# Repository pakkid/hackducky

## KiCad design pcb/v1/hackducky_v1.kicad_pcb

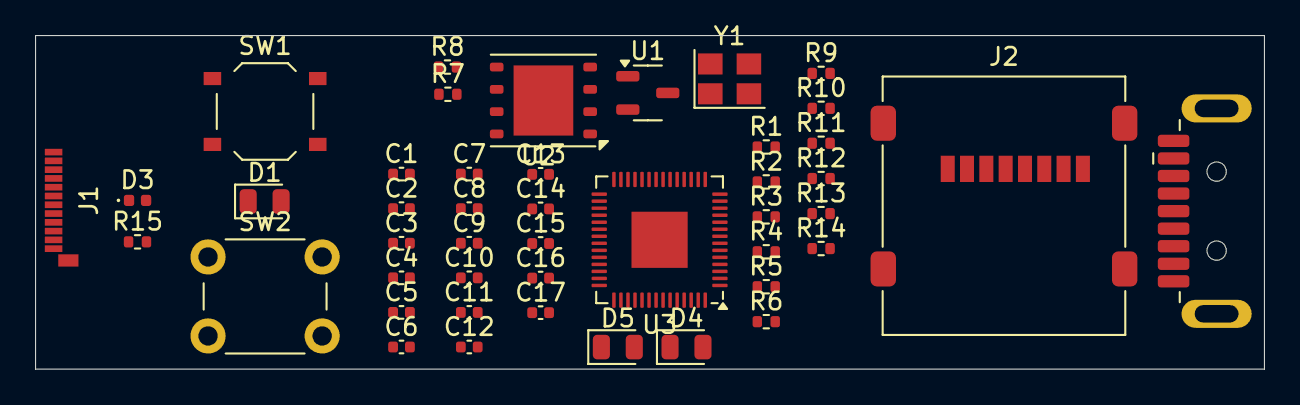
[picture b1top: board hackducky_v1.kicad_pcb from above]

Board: 2 copper layers, 70.0 x 19.0 mm, 45 parts (0 on the bottom side), 32 nets, no tracks yet.

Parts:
C1, C2: 15p; C_0402_1005Metric
C3, C4, C9, C10: 1u; C_0402_1005Metric
C5: 10u; C_0402_1005Metric
C6, C7, C8, C11, C12, C13, C14, C15, C16, C17: 100n; C_0402_1005Metric
D1: LED; LED_0805_2012Metric
D3: LED; LED_0402_1005Metric
D4, D5: S-LMBR340FT1G; D_0805_2012Metric
J1: USB_C_Receptacle_USB2.0_16P; USB_C_Plug_Molex_105444
J2: Micro_SD_Card; microSD_HC_Molex_47219-2001
J3: USB_A; USB3_A_Plug_Wuerth_692112030100_Horizontal
R1, R2: 5.1k; R_0402_1005Metric
R3, R5: 1k; R_0402_1005Metric
R4: 330; R_0402_1005Metric
R6: DNF; R_0402_1005Metric
R7, R8: 27.4; R_0402_1005Metric
R9, R10, R11, R12, R13, R14: 10k; R_0402_1005Metric
R15: 330?; R_0402_1005Metric
SW1: SW_Push; SW_Push_1P1T_XKB_TS-1187A
SW2: SW_Push; SW_PUSH_6mm
U1: XC6206PxxxMR; SOT-23-3
U2: W25Q64JVZPIQ; WSON-8-1EP_6x5mm_P1.27mm_EP3.4x4mm
U3: RP2040; QFN-56-1EP_7x7mm_P0.4mm_EP3.2x3.2mm
Y1: Crystal_GND23; Crystal_SMD_Abracon_ABM8G-4Pin_3.2x2.5mm

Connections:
+1V1: C7.1, C8.1, C9.1, U3.23 (DVDD), U3.45 (VREG_VOUT), U3.50 (DVDD)
+3V3: C4.1, C5.1, C6.1, C10.1, C11.1, C12.1, C13.1, C14.1, C15.1, C16.1, C17.1, J2.4 (VDD), R6.1, R9.1, R10.1, R11.1, R12.1, R13.1, R14.1, U1.2 (VO), U2.8 (VCC), U3.1 (IOVDD), U3.10 (IOVDD), U3.22 (IOVDD), U3.33 (IOVDD), U3.42 (IOVDD), U3.43 (ADC_AVDD), U3.44 (VREG_IN), U3.48 (USB_VDD), U3.49 (IOVDD)
+5V: C3.1, D1.2 (A), D4.1 (K), D5.1 (K), U1.3 (VI)
CLK: J2.5 (CLK), R12.2, U3.4 (GPIO2)
CS: J2.2 (DAT3/CD), R10.2, U3.7 (GPIO5)
D+: J1.A6 (D+), J3.3 (D+), R7.2
D-: J1.A7 (D-), J3.2 (D-), R8.2
GND: C1.1, C2.1, C3.2, C4.2, C5.2, C6.2, C7.2, C8.2, C9.2, C10.2, C11.2, C12.2, C13.2, C14.2, C15.2, C16.2, C17.2, J1.A1 (GND), J1.A12 (GND), J1.B1 (GND), J1.B12 (GND), J1.S1 (SHIELD), J2.6 (VSS), J2.9 (SHIELD), J3.4 (GND), J3.5 (Shield), R1.2, R2.2, R4.2, R15.2, SW1.1, SW2.2, U1.1 (GND), U2.4 (GND), U3.19 (TESTEN), U3.57 (GND), Y1.2, Y1.3
LED: D3.2 (A), U3.37 (GPIO25)
MISO: J2.7 (DAT0), R13.2, U3.6 (GPIO4)
MOSI: J2.3 (CMD), R11.2, U3.5 (GPIO3)
unnamed: C2.2, R3.1, Y1.4
unnamed: D1.1 (K), R4.1
unnamed: D3.1 (K), R15.1
unnamed: D4.2 (A), J1.A4 (VBUS), J1.A9 (VBUS), J1.B4 (VBUS), J1.B9 (VBUS)
unnamed: D5.2 (A), J3.1 (VBUS)
unnamed: J1.A5 (CC1), R1.1
unnamed: J1.B5 (CC2), R2.1
unnamed: J2.8 (DAT1), R14.2
unnamed: J2.1 (DAT2), R9.2
unnamed: R5.1, SW1.2
unnamed: R8.1, U3.46 (USB_DM)
unnamed: R7.1, U3.47 (USB_DP)
PUSH: SW2.1, U3.40 (GPIO28_ADC2)
QSPI_SCLK: U2.6 (CLK), U3.52 (QSPI_SCLK)
QSPI_SD0: U2.5 (DI(IO0)), U3.53 (QSPI_SD0)
QSPI_SD1: U2.2 (DO(IO1)), U3.55 (QSPI_SD1)
QSPI_SD2: U2.3 (IO2), U3.54 (QSPI_SD2)
QSPI_SD3: U2.7 (IO3), U3.51 (QSPI_SD3)
QSPI_SS: R5.2, R6.2, U2.1 (~CS), U3.56 (QSPI_SS)
XIN: C1.2, U3.20 (XIN), Y1.1
XOUT: R3.2, U3.21 (XOUT)

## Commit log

2025-03-13 edit stuff
